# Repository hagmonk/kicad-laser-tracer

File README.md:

# KiCad Laser Tracer

Generate SVGs from KiCad PCB files for laser cutting. A streamlined
workflow for producing two-sided boards accurately and repeatedly.

## Features

- Generates isolation paths (areas where copper needs to be removed)
  as filled SVG regions
- Uses KiCad's native boolean operations for accurate geometry
- Outputs separate SVG files for each copper layer plus edge cuts and
  drill points
- Targets xTool Studio but should be useful for Lightburn or other
  software

## Process Overview

This project was born from my desire to make my own FR4 PCBs at home
using the xTool F2 Ultra. Stephen Hawes did [a lot of
work](https://github.com/sphawes/fiber-laser-pcb-fab) that inspired
this project.

My goal was to do *everything* with the laser, including contours,
drilling, traces, and mask removal. It had to be a repeatable process
with high reliability, otherwise one may as well order from PCBway or
whatever.

`kicad-laser-tracer` produces SVGs that enable this entire process;
it's not just about generating paths for engraving isolation traces,
but making sure you can position the board accurately, flip for the
second side, and return the board to the right place for mask removal!

The complete process looks like this:

- *Fixturing*: mostly one-time setup so that you have a spoilboard
  to protect the base plate of the laser, and known good coordinates
  for positioning your SVGs. We cut a template based on known
  fiducials, inside of which is our PCB held to the template with
  tabs. The template can be flipped, and the PCB can be re-inserted in
  the template if required later.
- *Cutting and Engraving*: we can now cut the board profile, drill
  holes, and remove copper to isolate the PCB traces. The template is
  flipped and the process repeated for the back side if applicable.
- *Tin-plating*: we clean the assembly with IPA to remove laser schmoo
  and prepare the copper, then dunk in liquid tin to protect it.
- *Solder mask*: we use a silkscreen and apply solder mask followed by
  a UV cure for both sides.
- *Mask removal*: we re-install the template and remove solder mask,
  on both sides if applicable.
- *PCB removal*: the PCB can now be broken away from the template, the
  tabs filed, and it's ready for the SMD oven or soldering iron.

## Usage

### Requirements

- KiCad 5.0 - 9.0 installed
- [uv](https://docs.astral.sh/uv/) package manager

The CLI automatically detects your KiCad installation and uses KiCad's bundled Python - no manual configuration needed.

### Running

```
# install
uv tool install git+https://github.com/hagmonk/kicad-laser-tracer

# running against an example
kicad-laser-tracer --multi --all example/example.kicad_pcb
```

This produces SVGs for the front and back. Dragging one of these SVGs
into XCS produces a nice clean result with multiple layers.

XCS groups objects into layers by color, and I have assigned colors to
different KiCad layers for a consistent result. This is the order in
which they appear in XCS, which is *not* the order in which they
should be processed

* *Cyan* - `User.Comments` - I use this layer for the board template
  which captures the fiducials from the laser base plate.
* *Yellow* - `Mask` - curves for mask removal
* *Orange* - `Cu` - curves from the copper layer corresponding to
  through holes to be drilled
* *Black* - `Cu` - curves from the copper layer representing isolation
  traces
* *Green* - `Edge.Cuts` - the board outline itself, used for the final
  cut

Individual SVGs can be generated for different layers, although I
stronly encourage keeping all layers together so you're able to align
everything relative to your fiducials.

- `isolation_F_Cu.svg` - Front copper isolation paths
- `isolation_B_Cu.svg` - Back copper isolation paths
- `edge_cuts.svg` - Board outline
- `drill_holes.svg` - Drill hole locations (with `--drill` or `--all`)
- `solder_mask_*.svg` - Solder mask openings (with `--mask` or `--all`)
- `multi_color_pcb.svg` - Combined multi-layer SVG (with `--multi`)

## Laser setup

### Board selection

Stephen dialed in settings for the F1 Ultra, but these don't apply
cleanly to the much more powerful MOPA source in the F2 Ultra.
Additionally he stuck to FR1. My problem with FR1 is that I wanted to
do *everything* with the laser - including cutting and drilling. After
close to a week of trial and error to find settings that cut FR1
cleanly on the F2 Ultra, I gave up and switched to FR4.

The difference was magical. With FR4 I am able to get relatively clean
contours and drilled holes, with FR1 there is no way to cut or drill
using a laser that doesn't turn the inside of the board into a
carbonized mess. Delamination of traces has also disappeared as an
issue.

Good ventillation is a must for working with FR4, but you should have
excellent ventillation for laser cutting and engraving regardless. I
use the xTool AP2 vented through a window.

### xTool F2 Ultra settings

Disclaimer! Some of these settings are a bit hit & miss, and since I
last made a PCB, xTool Studio has been updated to include a much more
functional way of stepping the laser focus down per each pass.
Previously it was very broken. So I expect in the near future to
revise these for even cleaner results!

| Setting | Holes          | Isolation traces | Contour  | Mask            |
|---------|----------------|------------------|----------|-----------------|
| Op      | Engrave        | Engrave          | Cut      | Engrave         |
| Laser   | MOPA IR        | MOPA IR          | MOPA IR  | MOPA IR         |
| Power   | 60%            | 78%              | 80%      | 20%             |
| Speed   | 5000 mm/s      | 5000 mm/s        | 200 mm/s | 2000 mm/s       |
| Pass    | 10             | 7                | 15       | 20              |
| Lines   | 300            | 300              | -        | 300             |
| Mode    | Bi-directional | Uni-directional  | -        | Uni-directional |
| Pulse   | 500 ns         | 500 ns           | 500 ns   | 60 ns           |
| Freq    | 30 kHz         | 30 kHz           | 30 kHz   | 115 kHz         |
| Tabs    | -              | -                | 6 x 1 mm |                 |

### Spoilboard and fiducials

Producing a spoilboard is left as an exercise for the reader. I cut
some brass plate on the Carvera CNC with appropriate hole spacing for
the xTool F2 Ultra base plate. The holes are spaced 35mm apart with an
annoying missing hole in the middle. I use M4 studs from McMaster to
position the spoilboard. When the PCB template is cut, you'll remove
these studs and reinstall them through the holes in the template.

## Troubleshooting

### "Could not find KiCad's Python interpreter"

Ensure KiCad is installed in a standard location:
- **macOS**: `/Applications/KiCad/KiCad.app`
- **Linux**: `/usr` or `/usr/local`
- **Windows**: `C:\Program Files\KiCad`

### Debug messages from wxWidgets

The "Debug: Adding duplicate image handler" messages are harmless warnings from KiCad's libraries when running outside the GUI.

## Note on KiCad 10+

The SWIG-based `pcbnew` Python bindings are deprecated as of KiCad 9.0 and will be removed in KiCad 10.0 (February 2026). Future versions may migrate to KiCad's IPC API.

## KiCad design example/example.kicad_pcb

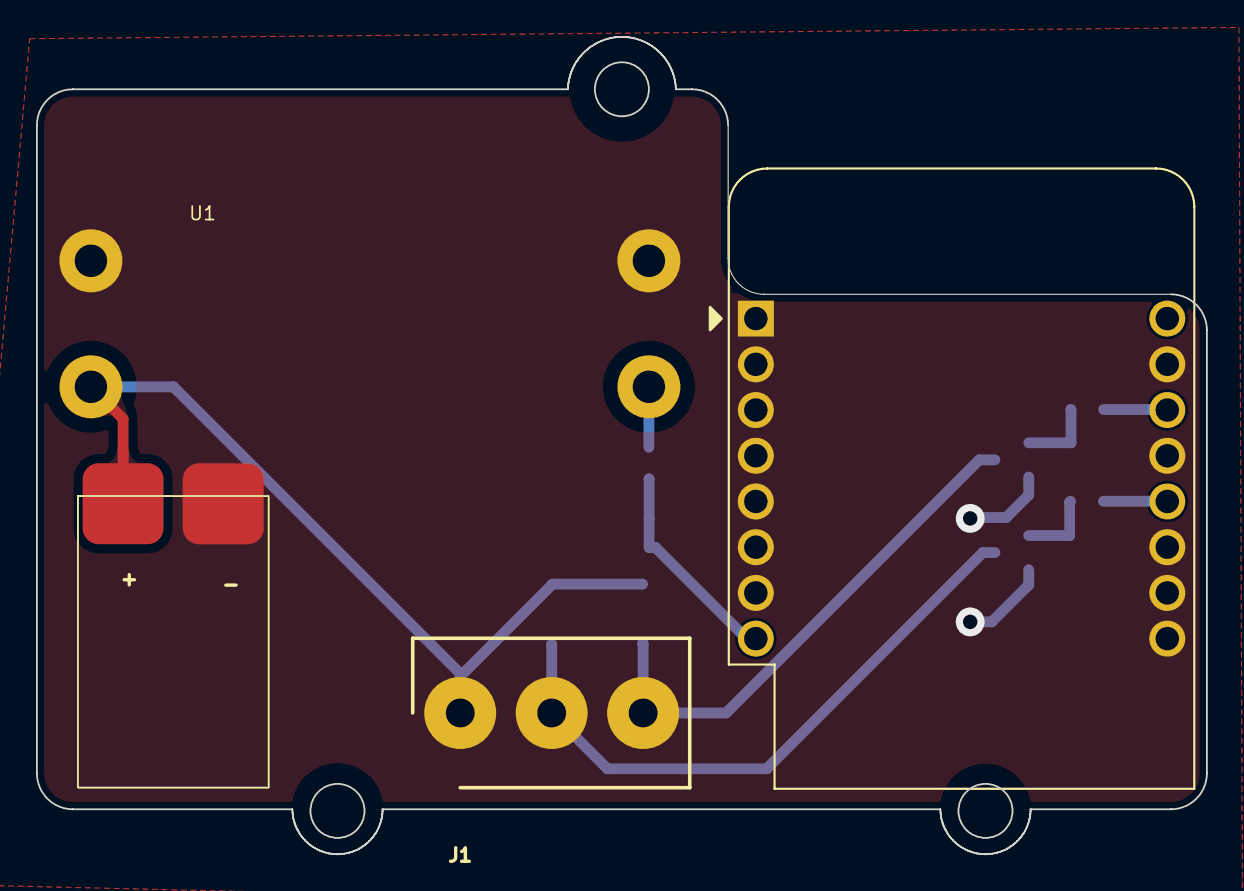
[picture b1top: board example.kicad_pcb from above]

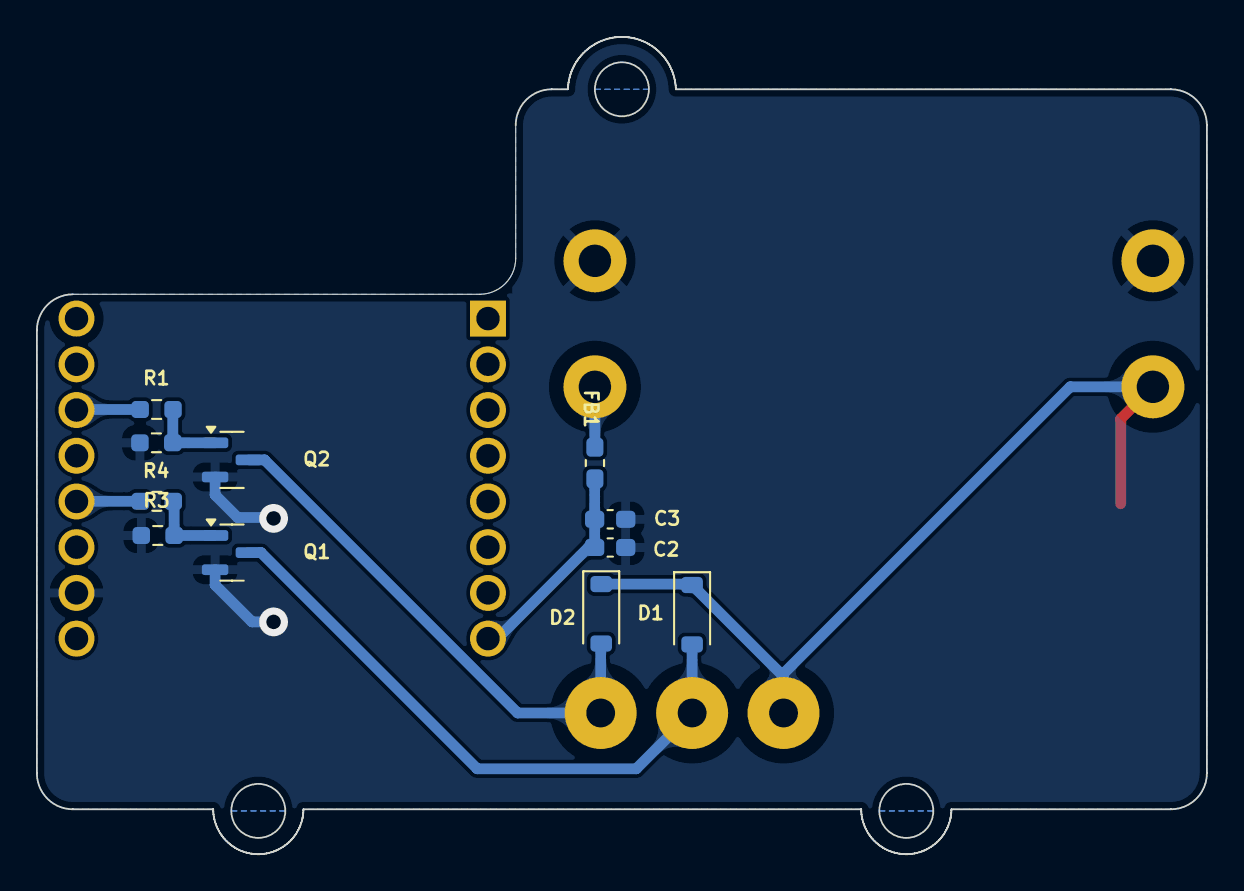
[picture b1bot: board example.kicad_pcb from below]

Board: 2 copper layers, 65.0 x 45.4 mm, 15 parts (11 on the bottom side), 8 nets.

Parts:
C2, C3: 22µF; C_0603_1608Metric_Pad1.08x0.95mm_HandSolder
D1, D2: 1N4007; D_SOD-123
FB1: 220Ω; L_0603_1608Metric_Pad1.05x0.95mm_HandSolder
J1: Conn_01x03_Socket; SHDR3W130P0X508_1X3_1524X815X1015P
PD_12V1: PDC004-PD
Q1, Q2: AO3400A; SOT-23
R1, R2: 220Ω; R_0603_1608Metric_Pad0.98x0.95mm_HandSolder
R3, R4: 10kΩ; R_0603_1608Metric_Pad0.98x0.95mm_HandSolder
U1: LM2596
U3: WEMOS_D1_mini; WEMOS_D1_mini_light

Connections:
/12V: D1.1 (K), D2.1 (K), J1.1, PD_12V1.1 (+12V), U1.3 (VIN+)
/LED_NEG1: D2.2 (A), J1.3, Q2.3 (D)
/LED_NEG2: D1.2 (A), J1.2, Q1.3 (D)
GND: C2.2, C3.2, PD_12V1.2 (GND), Q1.2 (S), Q2.2 (S), R3.2, R4.2, U1.1 (VOUT-), U1.4 (VIN-)
unnamed: Q1.1 (G), R2.1, R3.1
unnamed: Q2.1 (G), R1.1, R4.1
unnamed: FB1.1, U1.2 (VOUT+)
unnamed: C2.1, C3.1, FB1.2, U3.8 (3V3)

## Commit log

2025-12-27 initial
2026-01-12 make run with uvx
2026-01-18 add docs
